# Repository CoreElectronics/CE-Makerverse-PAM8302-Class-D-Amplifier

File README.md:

# Makerverse™ PAM8302 Class D Amplifier

This is the repo for the Core Electronics [Makerverse PAM8302 Class D Amplifier](https://core-electronics.com.au/catalog/product/view/sku/ce08263).

The PCB layout project requires KiCAD 6.0 or newer to view. The schematic is provided in PDF format in the Documents folder.

## License
This project is open source - please review the LICENSE.md file for further licensing information.

If you have any technical questions, or concerns about licensing, please contact technical support on the [Core Electronics forums](https://forum.core-electronics.com.au/).

*\"PiicoDev\" and the PiicoDev logo are trademarks of Core Electronics Pty Ltd.*

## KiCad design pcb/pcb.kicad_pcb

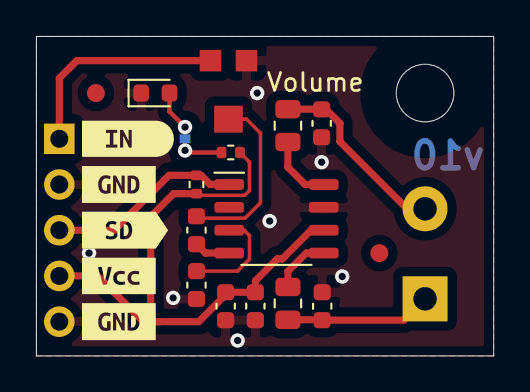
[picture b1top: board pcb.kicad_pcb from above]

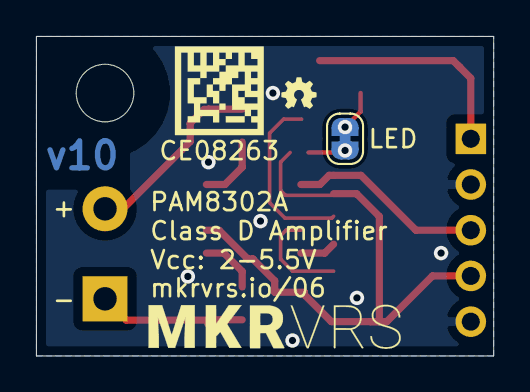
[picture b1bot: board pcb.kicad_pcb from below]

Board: 2 copper layers, 25.4 x 17.8 mm, 27 parts (4 on the bottom side), 13 nets.

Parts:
C1: 10uF; C_0603_1608Metric
C2, C3, C4: 1uF; C_0603_1608Metric
C6, C7: 1nF; C_0603_1608Metric
D1: LED; LED_0603_1608Metric
FB1, FB2: Ferrite_Bead; R_0805_2012Metric
FID1, FID2: Fiducial; Fiducial_1mm_Mask2mm
G1: LOGO_Makerverse; makerverse_logo_short_14.0x2.4mm
G2: Datamatrix; ce08263
H1: MountingHole; MountingHole_3.2mm_M3
J1: Conn_01x05; PinHeader_1x05_P2.54mm_Vertical
J2: Conn_01x02; TerminalBlock_MetzConnect_Type055_RT01502HDWU_1x02_P5.00mm_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
JP1: SolderJumper_2_Bridged; SolderJumper-2_P1.3mm_Bridged_RoundedPad1.0x1.5mm
LOGO1: Logo_Open_Hardware_Small; oshw
R1, R2: 4k7; R_0402_1005Metric
RV1: 50k; smdPot
U1: PAM8302AAD; SOP-8_3.9x4.9mm_P1.27mm
kibuzzard-6193131A, kibuzzard-6193131A#2, kibuzzard-61931308, kibuzzard-61931345, kibuzzard-61931355: G***; label

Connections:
/IN: J1.1, RV1.3
/\SD: J1.3, R1.1, U1.1 (~SD)
GND: C1.2, C2.2, C3.2, C6.2, C7.1, D1.1 (K), J1.2, J1.5, RV1.1, U1.7 (GND)
unnamed: C3.1, U1.3 (IN+)
unnamed: C4.1, U1.4 (IN-)
unnamed: C4.2, RV1.2
unnamed: C6.1, FB1.1, J2.1
unnamed: C7.2, FB2.1, J2.2
unnamed: D1.2 (A), JP1.2 (B)
unnamed: FB1.2, U1.5 (OUT+)
unnamed: FB2.2, U1.8 (OUT-)
unnamed: JP1.1 (A), R2.2
VCC: C1.1, C2.1, J1.4, R1.2, R2.1, U1.6 (VDD)

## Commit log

2022-10-13 add datasheet
